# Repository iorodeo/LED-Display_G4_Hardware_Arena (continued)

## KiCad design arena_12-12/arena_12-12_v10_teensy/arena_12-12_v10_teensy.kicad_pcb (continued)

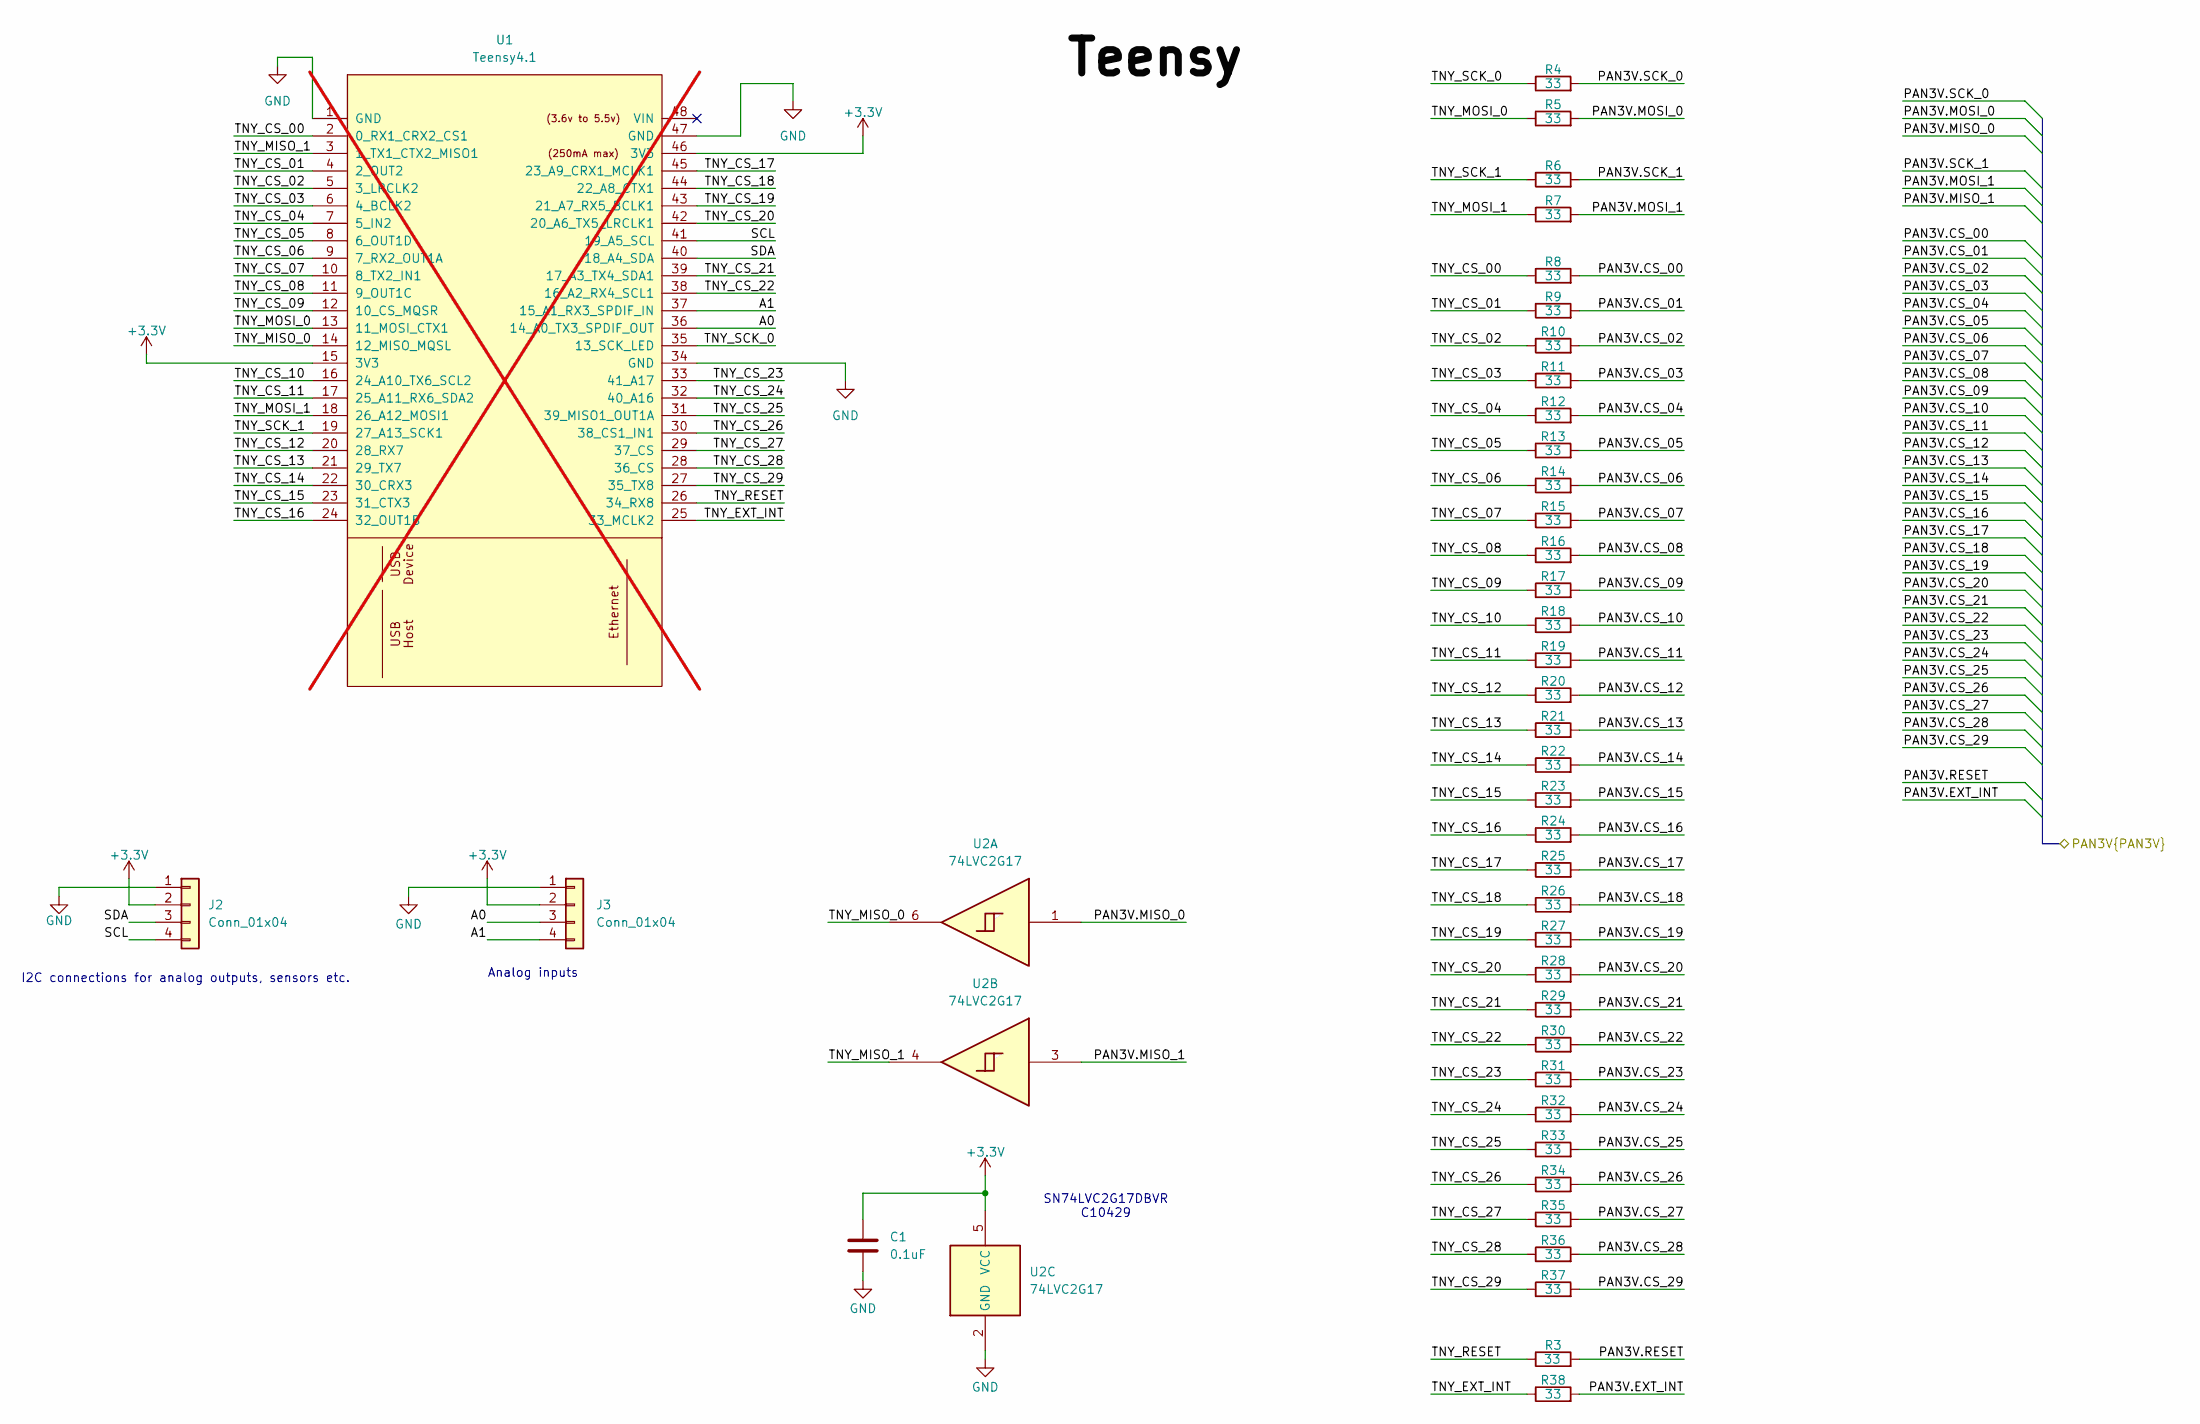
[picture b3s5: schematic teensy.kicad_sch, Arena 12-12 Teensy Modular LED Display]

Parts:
C1: 0.1uF; C_0402_1005Metric; MPN CL05B104KO5NNNC; DigiKey PN 1276-1001-2-ND
J2, J3: Conn_01x04; JST_SH_SM04B-SRSS-TB_1x04-1MP_P1.00mm_Horizontal; MPN SM04B-SRSS-TB; DigiKey PN 455-SM04B-SRSS-TBTR-ND
R3, R4, R5, R6, R7, R8, R9, R10, R11, R12, R13, R14, R15, R16, R17, R18, R19, R20, R21, R22, R23, R24, R25, R26, R27, R28, R29, R30, R31, R32, R33, R34, R35, R36, R37, R38: 33; R_0402_1005Metric; MPN 0402WGF330JTCE; LCSC Part # C25105
U1: Teensy4.1; Teensy41_outer_only; not fitted
U2: 74LVC2G17; SOT-23-6; MPN SN74LVC2G17DBVR; DigiKey PN 296-SN74LVC2G17DBVRTR-ND

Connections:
+3.3V: C1.1, J2.2, J3.2, U1.15 (3V3), U1.46 (3V3), U2.5 (VCC); also elsewhere on the board
/Level Shifters/PAN3V.CS_00: R8.2; also elsewhere on the board
/Level Shifters/PAN3V.CS_01: R9.2; also elsewhere on the board
/Level Shifters/PAN3V.CS_02: R10.2; also elsewhere on the board
/Level Shifters/PAN3V.CS_03: R11.2; also elsewhere on the board
/Level Shifters/PAN3V.CS_04: R12.2; also elsewhere on the board
/Level Shifters/PAN3V.CS_05: R13.2; also elsewhere on the board
/Level Shifters/PAN3V.CS_06: R14.2; also elsewhere on the board
/Level Shifters/PAN3V.CS_07: R15.2; also elsewhere on the board
/Level Shifters/PAN3V.CS_08: R16.2; also elsewhere on the board
/Level Shifters/PAN3V.CS_09: R17.2; also elsewhere on the board
/Level Shifters/PAN3V.CS_10: R18.2; also elsewhere on the board
/Level Shifters/PAN3V.CS_11: R19.2; also elsewhere on the board
/Level Shifters/PAN3V.CS_12: R20.2; also elsewhere on the board
/Level Shifters/PAN3V.CS_13: R21.2; also elsewhere on the board
/Level Shifters/PAN3V.CS_14: R22.2; also elsewhere on the board
/Level Shifters/PAN3V.CS_15: R23.2; also elsewhere on the board
/Level Shifters/PAN3V.CS_16: R24.2; also elsewhere on the board
/Level Shifters/PAN3V.CS_17: R25.2; also elsewhere on the board
/Level Shifters/PAN3V.CS_18: R26.2; also elsewhere on the board
/Level Shifters/PAN3V.CS_19: R27.2; also elsewhere on the board
/Level Shifters/PAN3V.CS_20: R28.2; also elsewhere on the board
/Level Shifters/PAN3V.CS_21: R29.2; also elsewhere on the board
/Level Shifters/PAN3V.CS_22: R30.2; also elsewhere on the board
/Level Shifters/PAN3V.CS_23: R31.2; also elsewhere on the board
/Level Shifters/PAN3V.CS_24: R32.2; also elsewhere on the board
/Level Shifters/PAN3V.CS_25: R33.2; also elsewhere on the board
/Level Shifters/PAN3V.CS_26: R34.2; also elsewhere on the board
/Level Shifters/PAN3V.CS_27: R35.2; also elsewhere on the board
/Level Shifters/PAN3V.CS_28: R36.2; also elsewhere on the board
/Level Shifters/PAN3V.CS_29: R37.2; also elsewhere on the board
/Level Shifters/PAN3V.EXT_INT: R38.2; also elsewhere on the board
/Level Shifters/PAN3V.MISO_0: U2.1; also elsewhere on the board
/Level Shifters/PAN3V.MISO_1: U2.3; also elsewhere on the board
/Level Shifters/PAN3V.MOSI_0: R5.2; also elsewhere on the board
/Level Shifters/PAN3V.MOSI_1: R7.2; also elsewhere on the board
/Level Shifters/PAN3V.RESET: R3.2; also elsewhere on the board
/Level Shifters/PAN3V.SCK_0: R4.2; also elsewhere on the board
/Level Shifters/PAN3V.SCK_1: R6.2; also elsewhere on the board
/Teensy/A0: J3.3, U1.36 (14_A0_TX3_SPDIF_OUT)
/Teensy/A1: J3.4, U1.37 (15_A1_RX3_SPDIF_IN)
/Teensy/SCL: J2.4, U1.41 (19_A5_SCL)
/Teensy/SDA: J2.3, U1.40 (18_A4_SDA)
/Teensy/TNY_CS_00: R8.1, U1.2 (0_RX1_CRX2_CS1)
/Teensy/TNY_CS_01: R9.1, U1.4 (2_OUT2)
/Teensy/TNY_CS_02: R10.1, U1.5 (3_LRCLK2)
/Teensy/TNY_CS_03: R11.1, U1.6 (4_BCLK2)
/Teensy/TNY_CS_04: R12.1, U1.7 (5_IN2)
/Teensy/TNY_CS_05: R13.1, U1.8 (6_OUT1D)
/Teensy/TNY_CS_06: R14.1, U1.9 (7_RX2_OUT1A)
/Teensy/TNY_CS_07: R15.1, U1.10 (8_TX2_IN1)
/Teensy/TNY_CS_08: R16.1, U1.11 (9_OUT1C)
/Teensy/TNY_CS_09: R17.1, U1.12 (10_CS_MQSR)
/Teensy/TNY_CS_10: R18.1, U1.16 (24_A10_TX6_SCL2)
/Teensy/TNY_CS_11: R19.1, U1.17 (25_A11_RX6_SDA2)
/Teensy/TNY_CS_12: R20.1, U1.20 (28_RX7)
/Teensy/TNY_CS_13: R21.1, U1.21 (29_TX7)
/Teensy/TNY_CS_14: R22.1, U1.22 (30_CRX3)
/Teensy/TNY_CS_15: R23.1, U1.23 (31_CTX3)
/Teensy/TNY_CS_16: R24.1, U1.24 (32_OUT1B)
/Teensy/TNY_CS_17: R25.1, U1.45 (23_A9_CRX1_MCLK1)
/Teensy/TNY_CS_18: R26.1, U1.44 (22_A8_CTX1)
/Teensy/TNY_CS_19: R27.1, U1.43 (21_A7_RX5_BCLK1)
/Teensy/TNY_CS_20: R28.1, U1.42 (20_A6_TX5_LRCLK1)
/Teensy/TNY_CS_21: R29.1, U1.39 (17_A3_TX4_SDA1)
/Teensy/TNY_CS_22: R30.1, U1.38 (16_A2_RX4_SCL1)
/Teensy/TNY_CS_23: R31.1, U1.33 (41_A17)
/Teensy/TNY_CS_24: R32.1, U1.32 (40_A16)
/Teensy/TNY_CS_25: R33.1, U1.31 (39_MISO1_OUT1A)
/Teensy/TNY_CS_26: R34.1, U1.30 (38_CS1_IN1)
/Teensy/TNY_CS_27: R35.1, U1.29 (37_CS)
/Teensy/TNY_CS_28: R36.1, U1.28 (36_CS)
/Teensy/TNY_CS_29: R37.1, U1.27 (35_TX8)
/Teensy/TNY_EXT_INT: R38.1, U1.25 (33_MCLK2)
/Teensy/TNY_MISO_0: U1.14 (12_MISO_MQSL), U2.6
/Teensy/TNY_MISO_1: U1.3 (1_TX1_CTX2_MISO1), U2.4
/Teensy/TNY_MOSI_0: R5.1, U1.13 (11_MOSI_CTX1)
/Teensy/TNY_MOSI_1: R7.1, U1.18 (26_A12_MOSI1)
/Teensy/TNY_RESET: R3.1, U1.26 (34_RX8)
/Teensy/TNY_SCK_0: R4.1, U1.35 (13_SCK_LED)
/Teensy/TNY_SCK_1: R6.1, U1.19 (27_A13_SCK1)
GND: C1.2, J2.1, J3.1, U1.1 (GND), U1.34 (GND), U1.47 (GND), U2.2 (GND); also elsewhere on the board

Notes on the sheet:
Analog inputs
I2C connections for analog outputs, sensors etc.
SN74LVC2G17DBVR C10429
